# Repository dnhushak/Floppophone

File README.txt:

_       _                               _ 
  /\/\   ___  _ __  _ __  _   _  /_\   __| |_   ____ _ _ __   ___ ___  __| |
 /    \ / _ \| '_ \| '_ \| | | |//_\\ / _` \ \ / / _` | '_ \ / __/ _ \/ _` |
/ /\/\ \ (_) | |_) | |_) | |_| /  _  \ (_| |\ V / (_| | | | | (_|  __/ (_| |
\/    \/\___/| .__/| .__/ \__, \_/ \_/\__,_| \_/ \__,_|_| |_|\___\___|\__,_|
             |_|   |_|    |___/                                             

by Sammy1Am

Moppy is a M_usical Fl_oppy controller program built for the Arduino UNO.

-- NEW VERSION --
Check out MoppyAdvanced at :
https://github.com/SammyIAm/Moppy/tree/moppy-advanced
Lots of new features, and a few stability fixes.

This version attempts to improve upon the original Moppy by adding additional functionality including:

- MIDI-IN support
- Per-channel output control
- Support for multiple Arduinos/MIDI devices

        __  ___                     ___    __       
| |\ | /__`  |   /\  |    |     /\   |  | /  \ |\ | 
| | \| .__/  |  /~~\ |___ |___ /~~\  |  | \__/ | \| 

The Arduino code requires the TimeOne library available here: http://www.arduino.cc/playground/Code/Timer1

You will need to follow the directions in the appropriate Java/SerialDrivers folder for your system to install the serial drivers prior to running Moppy.

Upload the included Arduino code to the Arduino of your choice, and open up the included Java code in your favorite IDE.  This code includes a NetBeans project for your convenience, so you should be able to open the project directly in NetBeans.

           __   __             __   ___ 
|__|  /\  |__) |  \ |  |  /\  |__) |__  
|  | /~~\ |  \ |__/ |/\| /~~\ |  \ |___ 

I built Moppy using an Arduino UNO, though it should work just fine on most Arduinos.  The pins are connected in pairs to floppy drives as follows: Even pins (2,4,6...) are connected to each drive's STEP pin, the matching odd pins (3,5,7...) are connected to the each drive's DIRECTION control pin.  So the first floppy would be connected to pin 2 & 3, the second floppy to 4 & 5, and so on.

Some pinout information can be found here: http://pinouts.ru/Storage/InternalDisk_pinout.shtml

Make sure you ground the correct drive-select pin, or the drive won't respond to any input (just connect the drive-select pin on the floppy to the pin directly below it).  You can tell when you have the right drive selected, because the light on the front of the drive will come on.  

Also, it's VERY IMPORTANT that your Arduino is grounded with the drives, or the drives will not register the pulses correctly.  To do this, make sure that the GND pin on the Arduino is connected to the odd-numbered pin below the STEP pin on the floppy (i.e. if the STEP pin is 20, connect the Audnio's GND pin to Floppy-pin 19).  You might need to do this for the DIRECTION pin as well (I did it for both, but I don't know if it's required).

 __   __        ___    __        __       ___    __       
/  ` /  \ |\ | |__  | / _` |  | |__)  /\   |  | /  \ |\ | 
\__, \__/ | \| |    | \__> \__/ |  \ /~~\  |  | \__/ | \| 

- Open up the code in NetBeans (or your favorite IDE) and run it.  Alternatively, you can build the MoppyDesk.jar file and run that.
- Select the COM port that the Arduino is hooked up to from the "Arduino Port" drop-down.  You will need to have this configured before you launch MoppyDesk.
- Click the "Connect" button to create a new Sequencer connected to the specified COM port.
- Click the "Load Sequence" button and select a suitable MIDI file (see below).
- Click "Start" to start playback (if all goes well).  
- The Stop/Reset button will stop playback and reset the drives.  Pressing "Start" again will resume from where the sequencer left off.  You will need to reload the MIDI to start from the beginning.

         __       ___    __   __  
 |\/| | |  \ |     |  | |__) /__` 
 |  | | |__/ |     |  | |    .__/ 

- MIDI files should have one MIDI channel for each controller pin on the Arduino.  Channel 1 will be sent to pin2, channel 2 to pin4, &c.
- Each drive can only play a single note at a time.
- The software will only attempt to play notes between C1 and B4.  Floppy drives don't seem to respond well to notes outside of this range (especially higher).
- Generally shorter notes tend to sound better, as longer notes are marred by the read-heads changing directions repeatedly.

Cross your fingers, and enjoy!

--HELP/CONTRIBUTIONS--

https://github.com/SammyIAm/Moppy

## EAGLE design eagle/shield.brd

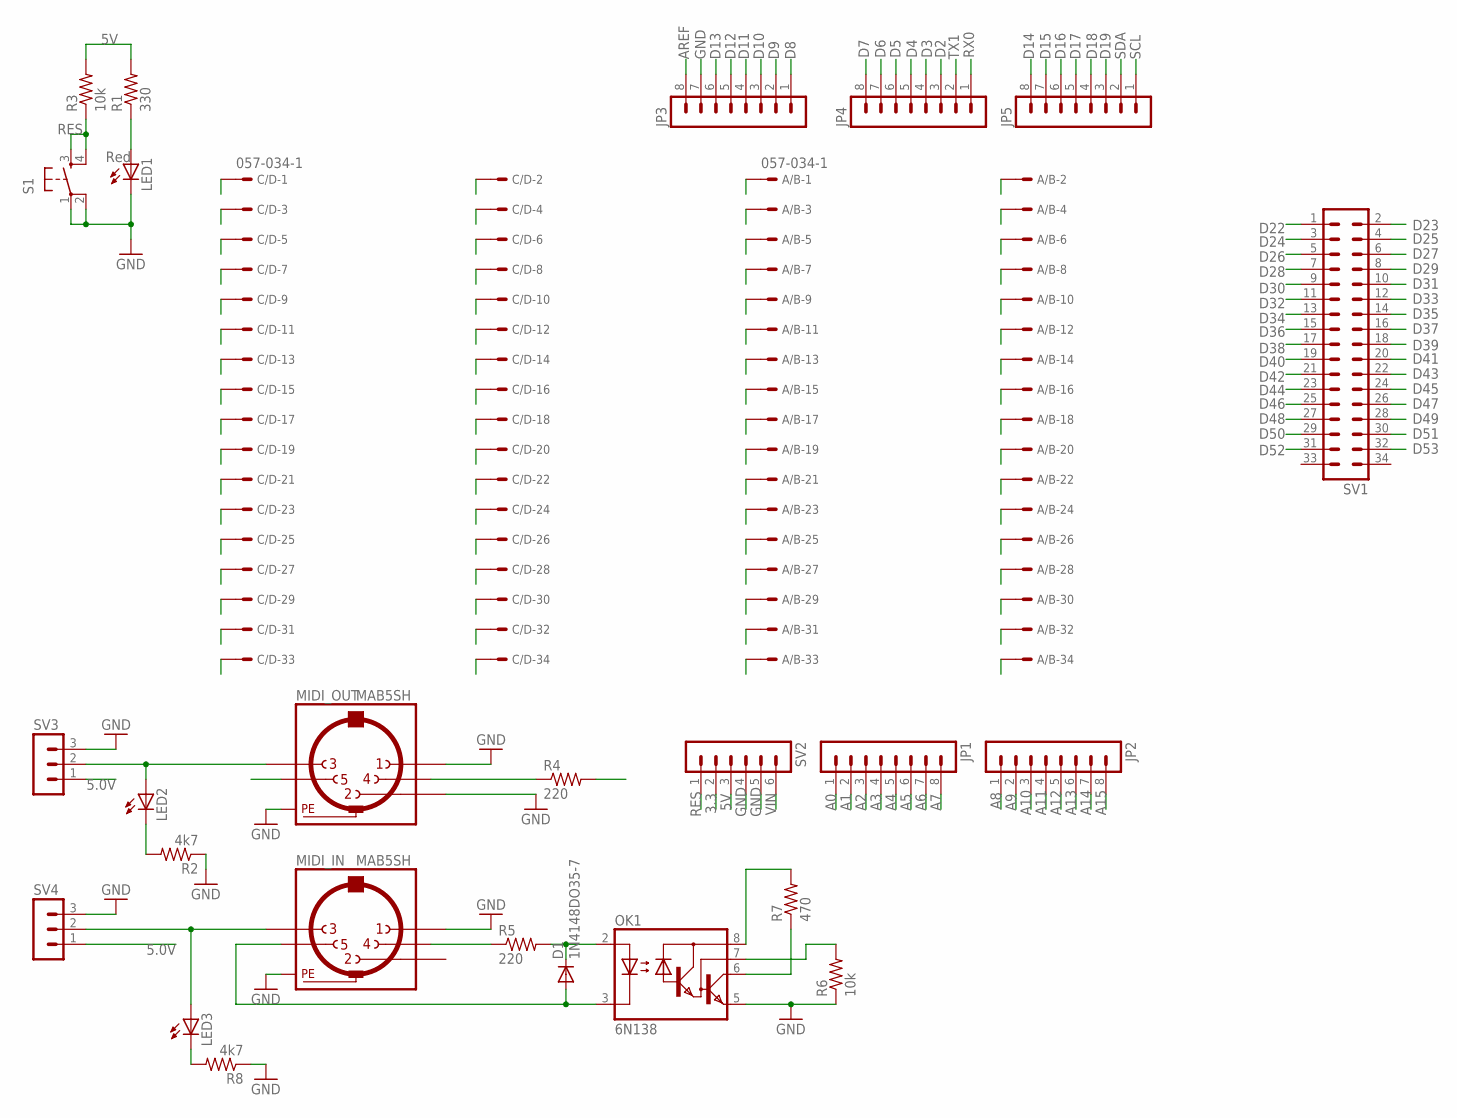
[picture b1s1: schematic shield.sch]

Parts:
A/B: 057-034-1
C/D: 057-034-1
D1: 1N4148DO35-7; DO35-7
JP1, JP2, JP3, JP4, JP5: MA08-1
LED1: Red; LED5MM
LED2, LED3: LEDLSU260; LSU260
MIDI_IN: MAB5SH
MIDI_OUT: MAB5SH
OK1: 6N138; DIL08
R1: 330; AXIAL-0.3
R2, R8: 4k7; 0204/7
R3: 10k; AXIAL-0.3
R4, R5: 220; 0204/7
R6: 10k; 0204/7
R7: 470; 0204/7
S1: TAC_SWITCHPTH; TACTILE-PTH
SV1: MA17-2
SV2: MA06-1
SV3, SV4: MA03-1

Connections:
3.3: SV2.2
5V: A/B.33, C/D.2, C/D.33, OK1.8 (VCC), R1.P$2 (2), R3.P$2 (2), R4.2, R7.2, SV2.3, SV3.1, SV4.1
A0: JP1.1
A1: JP1.2
A2: JP1.3
A3: JP1.4
A4: C/D.9, JP1.5
A5: C/D.11, JP1.6
A6: C/D.13, JP1.7
A7: C/D.15, JP1.8
A8: C/D.17, JP2.1
A9: C/D.19, JP2.2
A10: C/D.21, JP2.3
A11: C/D.23, JP2.4
A12: C/D.25, JP2.5
A13: C/D.27, JP2.6
A14: C/D.29, JP2.7
A15: C/D.31, JP2.8
AREF: JP3.8
D2: A/B.26, JP4.3
D3: A/B.24, JP4.4
D4: A/B.22, JP4.5
D5: A/B.20, JP4.6
D6: A/B.18, JP4.7
D7: A/B.16, JP4.8
D8: A/B.14, JP3.1
D9: A/B.12, JP3.2
D10: A/B.10, JP3.3
D11: A/B.8, JP3.4
D12: A/B.6, JP3.5
D13: A/B.4, JP3.6
D14: JP5.8
D15: JP5.7
D16: JP5.6
D17: JP5.5
D18: JP5.4, MIDI_OUT.5
D19: JP5.3, OK1.6 (VO), R7.1
D22: A/B.9, SV1.1
D23: A/B.11, SV1.2
D24: A/B.13, SV1.3
D25: A/B.15, SV1.4
D26: A/B.17, SV1.5
D27: A/B.19, SV1.6
D28: A/B.21, SV1.7
D29: A/B.31, SV1.8
D30: A/B.29, SV1.9
D31: A/B.27, SV1.10
D32: A/B.25, SV1.11
D33: A/B.23, SV1.12
D34: C/D.4, SV1.13
D35: C/D.6, SV1.14
D36: C/D.8, SV1.15
D37: C/D.10, SV1.16
D38: C/D.12, SV1.17
D39: C/D.14, SV1.18
D40: C/D.16, SV1.19
D41: C/D.18, SV1.20
D42: C/D.20, SV1.21
D43: C/D.22, SV1.22
D44: C/D.24, SV1.23
D45: C/D.26, SV1.24
D46: SV1.25
D47: SV1.26
D48: SV1.27
D49: SV1.28
D50: SV1.29
D51: SV1.30
D52: SV1.31
D53: SV1.32
GND: A/B.34, C/D.34, JP3.7, LED1.K (C), MIDI_IN.1, MIDI_IN.PE, MIDI_IN.PE@ (PE), MIDI_OUT.1, MIDI_OUT.2, MIDI_OUT.PE, MIDI_OUT.PE@ (PE), OK1.5 (GND), R2.1, R6.1, R8.1, S1.1, S1.2, SV2.4, SV2.5, SV3.3, SV4.3
unnamed: LED3.A, MIDI_IN.3, SV4.2
unnamed: LED2.A, MIDI_OUT.3, SV3.2
unnamed: MIDI_OUT.4, R4.1
unnamed: LED2.K (C), R2.2
unnamed: D1.C, OK1.2 (A), R5.2
unnamed: MIDI_IN.4, R5.1
unnamed: D1.A, MIDI_IN.5, OK1.3 (C)
unnamed: OK1.7 (VB), R6.2
unnamed: LED3.K (C), R8.2
unnamed: LED1.A, R1.P$1 (1)
RES: R3.P$1 (1), S1.3, S1.4, SV2.1
RX0: JP4.1
SCL: JP5.1
SDA: JP5.2
TX1: JP4.2
VIN: SV2.6

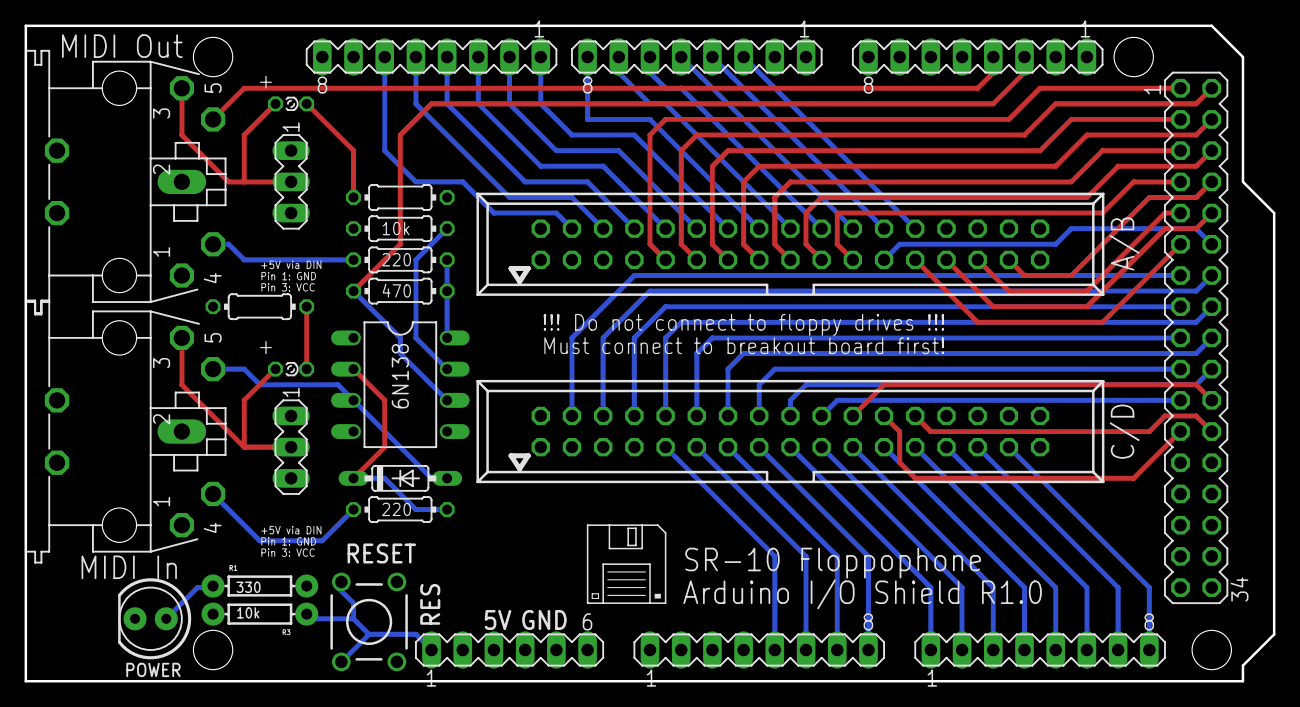
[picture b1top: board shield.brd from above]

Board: 2 copper layers, 101.6 x 53.3 mm, 27 parts (0 on the bottom side), 63 nets.

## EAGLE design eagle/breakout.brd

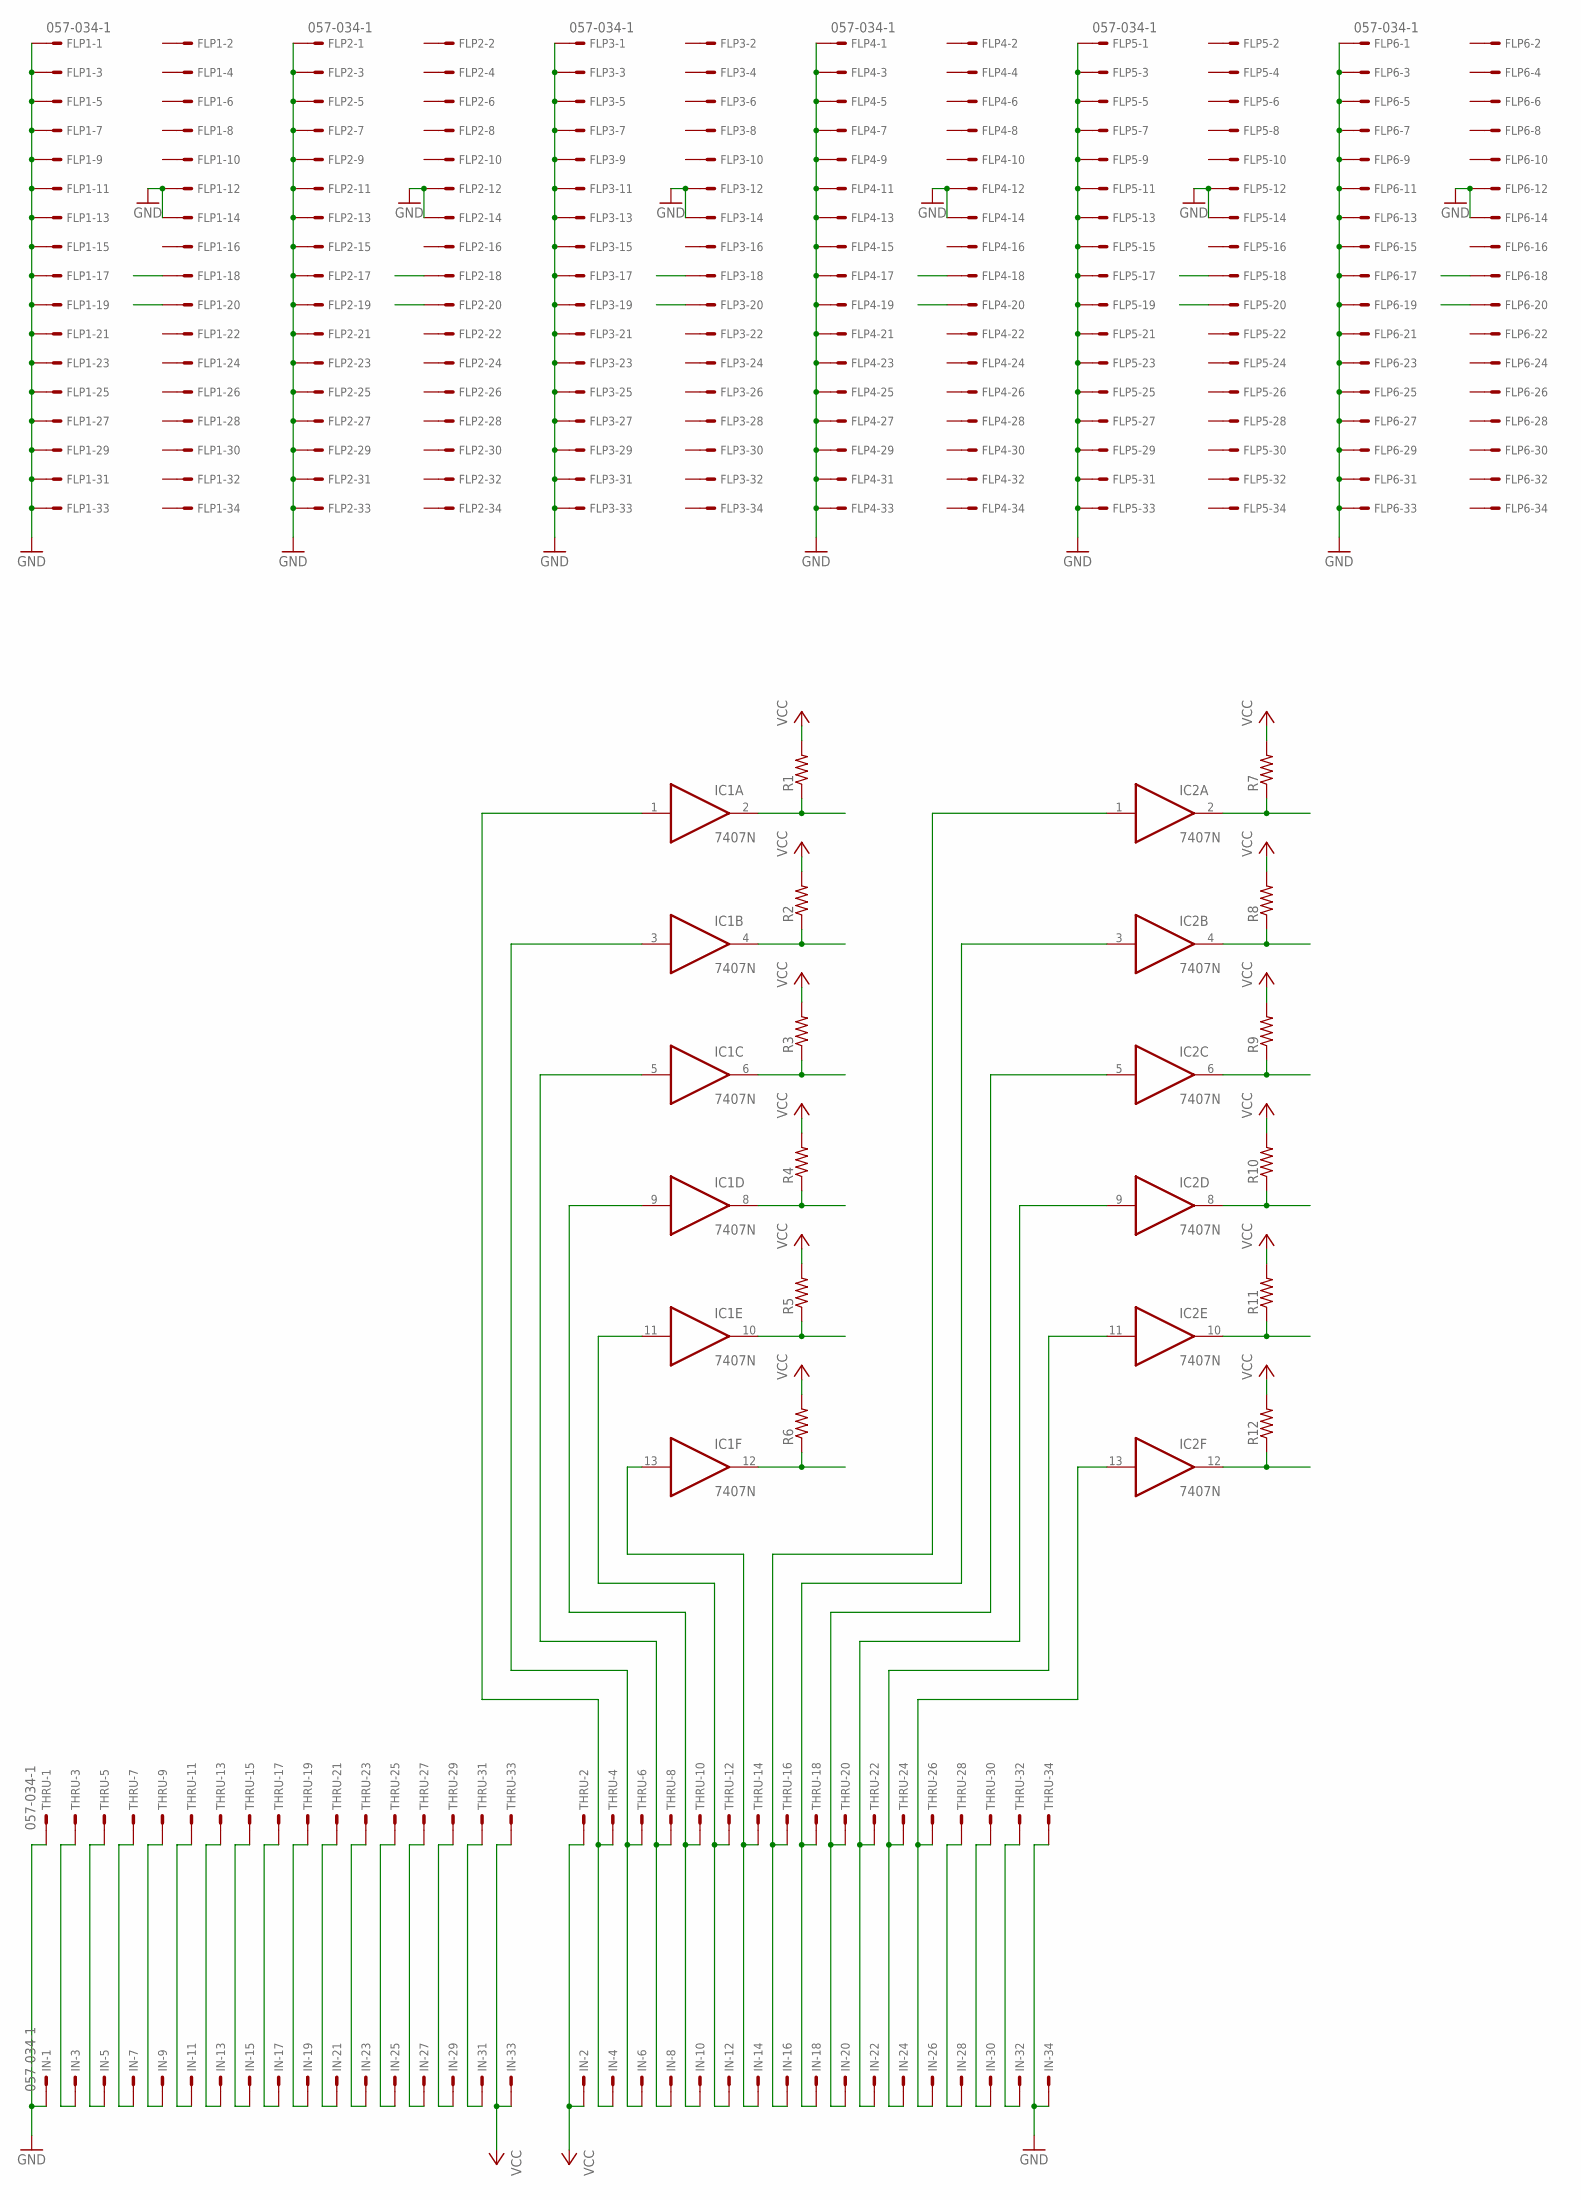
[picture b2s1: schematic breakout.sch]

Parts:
FLP1, FLP2, FLP3, FLP4, FLP5, FLP6: 057-034-1
IC1, IC2: 7407N; DIL14
IN: 057-034-1
R1, R2, R3, R4, R5, R6, R7, R8, R9, R10, R11, R12: R-US_0204/7; 0204/7
THRU: 057-034-1

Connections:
DIRECTION_1: FLP1.18, IC1.2 (O), R1.1
DIRECTION_2: FLP2.18, IC1.6 (O), R3.1
DIRECTION_3: FLP3.18, IC1.10 (O), R5.1
DIRECTION_4: FLP4.18, IC2.2 (O), R7.1
DIRECTION_5: FLP5.18, IC2.6 (O), R9.1
DIRECTION_6: FLP6.18, IC2.10 (O), R11.1
GND: FLP1.1, FLP1.3, FLP1.5, FLP1.7, FLP1.9, FLP1.11, FLP1.12, FLP1.13, FLP1.14, FLP1.15, FLP1.17, FLP1.19, FLP1.21, FLP1.23, FLP1.25, FLP1.27, FLP1.29, FLP1.31, FLP1.33, FLP2.1, FLP2.3, FLP2.5, FLP2.7, FLP2.9, FLP2.11, FLP2.12, FLP2.13, FLP2.14, FLP2.15, FLP2.17, FLP2.19, FLP2.21, FLP2.23, FLP2.25, FLP2.27, FLP2.29, FLP2.31, FLP2.33, FLP3.1, FLP3.3, FLP3.5, FLP3.7, FLP3.9, FLP3.11, FLP3.12, FLP3.13, FLP3.14, FLP3.15, FLP3.17, FLP3.19, FLP3.21, FLP3.23, FLP3.25, FLP3.27, FLP3.29, FLP3.31, FLP3.33, FLP4.1, FLP4.3, FLP4.5, FLP4.7, FLP4.9, FLP4.11, FLP4.12, FLP4.13, FLP4.14, FLP4.15, FLP4.17, FLP4.19, FLP4.21, FLP4.23, FLP4.25, FLP4.27, FLP4.29, FLP4.31, FLP4.33, FLP5.1, FLP5.3, FLP5.5, FLP5.7, FLP5.9, FLP5.11, FLP5.12, FLP5.13, FLP5.14, FLP5.15, FLP5.17, FLP5.19, FLP5.21, FLP5.23, FLP5.25, FLP5.27, FLP5.29, FLP5.31, FLP5.33, FLP6.1, FLP6.3, FLP6.5, FLP6.7, FLP6.9, FLP6.11, FLP6.12, FLP6.13, FLP6.14, FLP6.15, FLP6.17, FLP6.19, FLP6.21, FLP6.23, FLP6.25, FLP6.27, FLP6.29, FLP6.31, FLP6.33, IC1.7 (GND), IC2.7 (GND), IN.1, IN.34, THRU.1, THRU.34
unnamed: IC1.1 (I), IN.4, THRU.4
unnamed: IC1.3 (I), IN.6, THRU.6
unnamed: IC1.5 (I), IN.8, THRU.8
unnamed: IC1.9 (I), IN.10, THRU.10
unnamed: IC1.11 (I), IN.12, THRU.12
unnamed: IC1.13 (I), IN.14, THRU.14
unnamed: IC2.1 (I), IN.16, THRU.16
unnamed: IC2.3 (I), IN.18, THRU.18
unnamed: IC2.5 (I), IN.20, THRU.20
unnamed: IC2.9 (I), IN.22, THRU.22
unnamed: IC2.11 (I), IN.24, THRU.24
unnamed: IC2.13 (I), IN.26, THRU.26
unnamed: IN.28, THRU.28
unnamed: IN.30, THRU.30
unnamed: IN.32, THRU.32
unnamed: IN.3, THRU.3
unnamed: IN.5, THRU.5
unnamed: IN.7, THRU.7
unnamed: IN.9, THRU.9
unnamed: IN.11, THRU.11
unnamed: IN.13, THRU.13
unnamed: IN.15, THRU.15
unnamed: IN.17, THRU.17
unnamed: IN.19, THRU.19
unnamed: IN.21, THRU.21
unnamed: IN.23, THRU.23
unnamed: IN.25, THRU.25
unnamed: IN.27, THRU.27
unnamed: IN.29, THRU.29
unnamed: IN.31, THRU.31
STEP_1: FLP1.20, IC1.4 (O), R2.1
STEP_2: FLP2.20, IC1.8 (O), R4.1
STEP_3: FLP3.20, IC1.12 (O), R6.1
STEP_4: FLP4.20, IC2.4 (O), R8.1
STEP_5: FLP5.20, IC2.8 (O), R10.1
STEP_6: FLP6.20, IC2.12 (O), R12.1
VCC: IC1.14 (VCC), IC2.14 (VCC), IN.2, IN.33, R1.2, R2.2, R3.2, R4.2, R5.2, R6.2, R7.2, R8.2, R9.2, R10.2, R11.2, R12.2, THRU.2, THRU.33

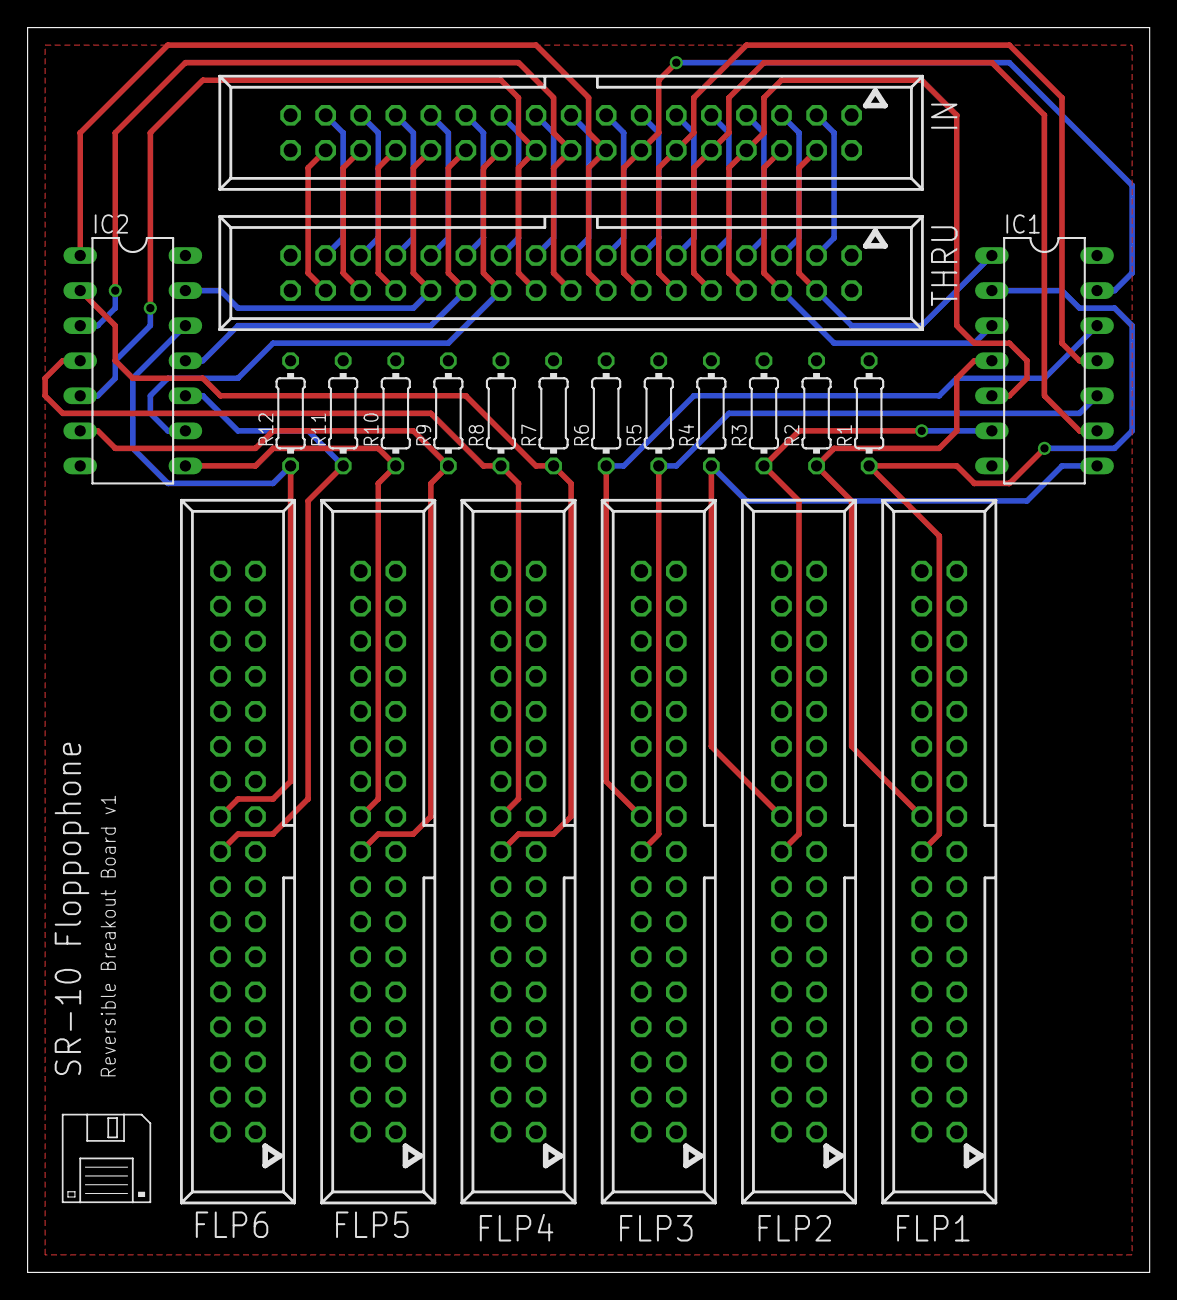
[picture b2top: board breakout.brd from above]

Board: 2 copper layers, 81.3 x 90.2 mm, 22 parts (0 on the bottom side), 44 nets.

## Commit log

2014-10-18 Got rid of the desktop MIDI reader
2014-10-19 Finished breakout board and shield
2014-10-19 Removed old shield
2020-01-18 Cleaned up

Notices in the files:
parts and their libraries:
SparkFun-Aesthetics: Licensing: Creative Commons ShareAlike 4.0 International - https://creativecommons.org/licenses/by-sa/4.0
